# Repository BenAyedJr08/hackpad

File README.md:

# JR4 Macropad
to get an introduction to robotics, i decided to make a simple design of a pcb with 4 switches where i added some basic shortcuts for daily use.
# BOM :
- 1 SEED XIAO RP2040
- 4 MX switches
- 2 SK6812 rgb diodes
# Schematics :

# PCB :

# CAD :

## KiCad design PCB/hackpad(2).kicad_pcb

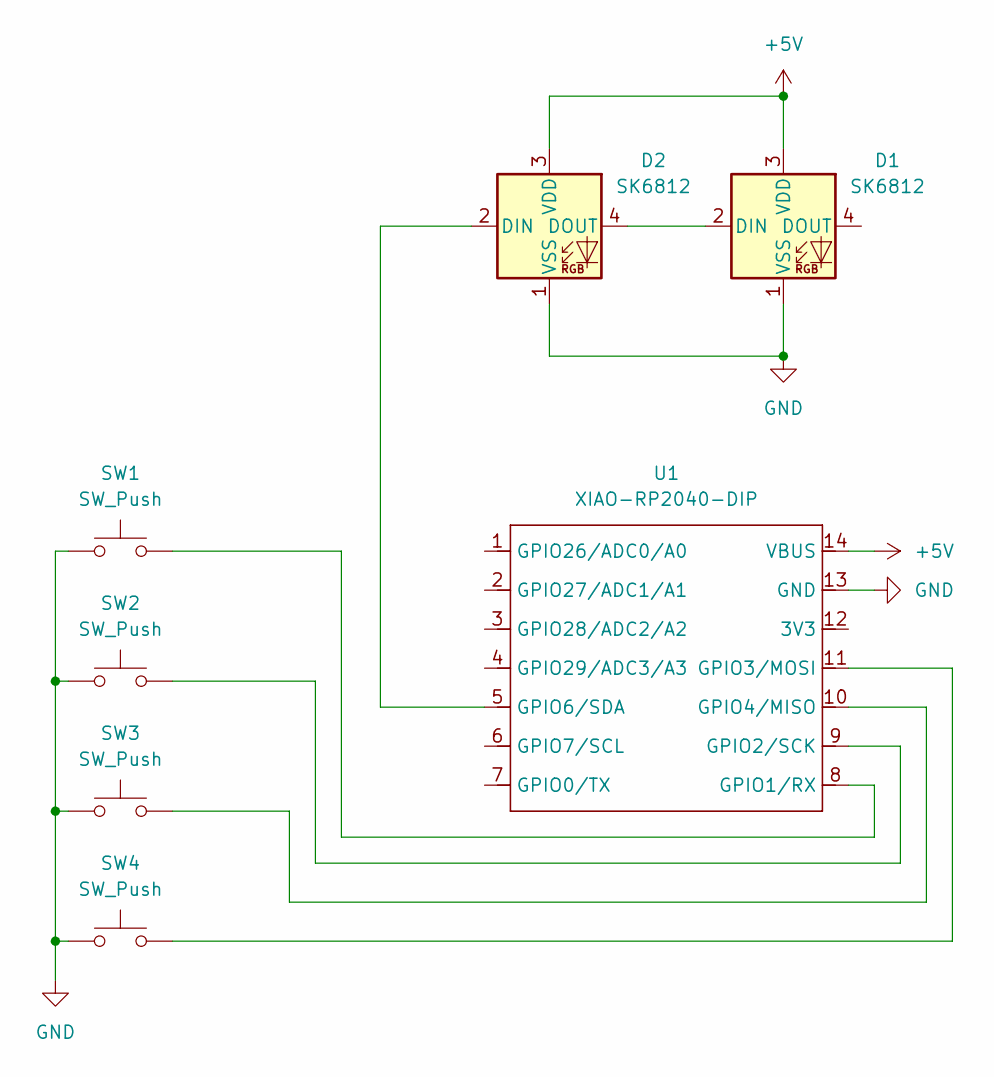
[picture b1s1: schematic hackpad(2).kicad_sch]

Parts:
D1, D2: SK6812; SK6812MINI-E_fixed
SW1, SW2, SW3, SW4: SW_Push; SW_Cherry_MX_1.00u_PCB
U1: XIAO-RP2040-DIP

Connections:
+5V: D1.3 (VDD), D2.3 (VDD), U1.14 (VBUS)
GND: D1.1 (VSS), D2.1 (VSS), SW1.1, SW2.1, SW3.1, SW4.1, U1.13 (GND)
unnamed: D1.2 (DIN), D2.4 (DOUT)
unnamed: D2.2 (DIN), U1.5 (GPIO6/SDA)
unnamed: SW1.2, U1.8 (GPIO1/RX)
unnamed: SW2.2, U1.9 (GPIO2/SCK)
unnamed: SW4.2, U1.11 (GPIO3/MOSI)
unnamed: SW3.2, U1.10 (GPIO4/MISO)

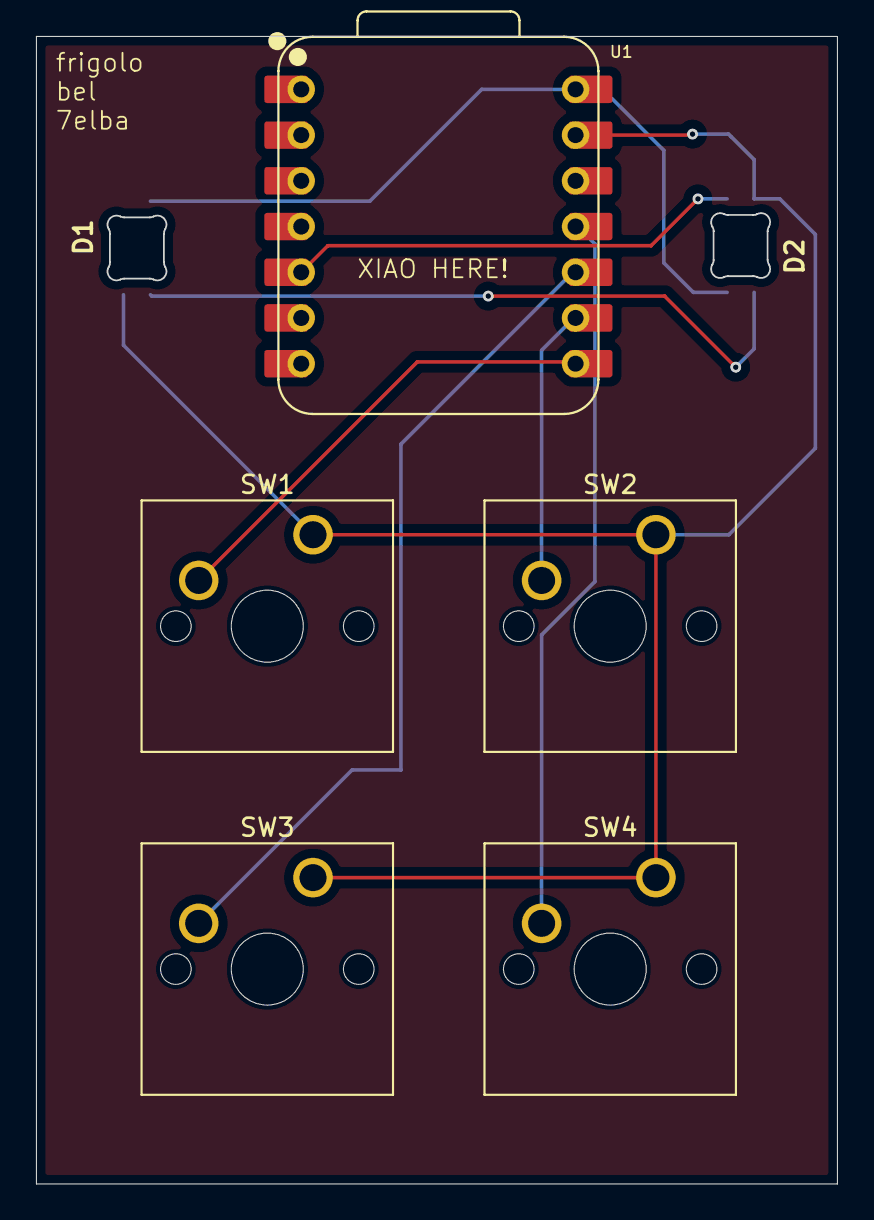
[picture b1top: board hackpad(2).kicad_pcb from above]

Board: 2 copper layers, 44.5 x 63.8 mm, 7 parts (0 on the bottom side), 8 nets.

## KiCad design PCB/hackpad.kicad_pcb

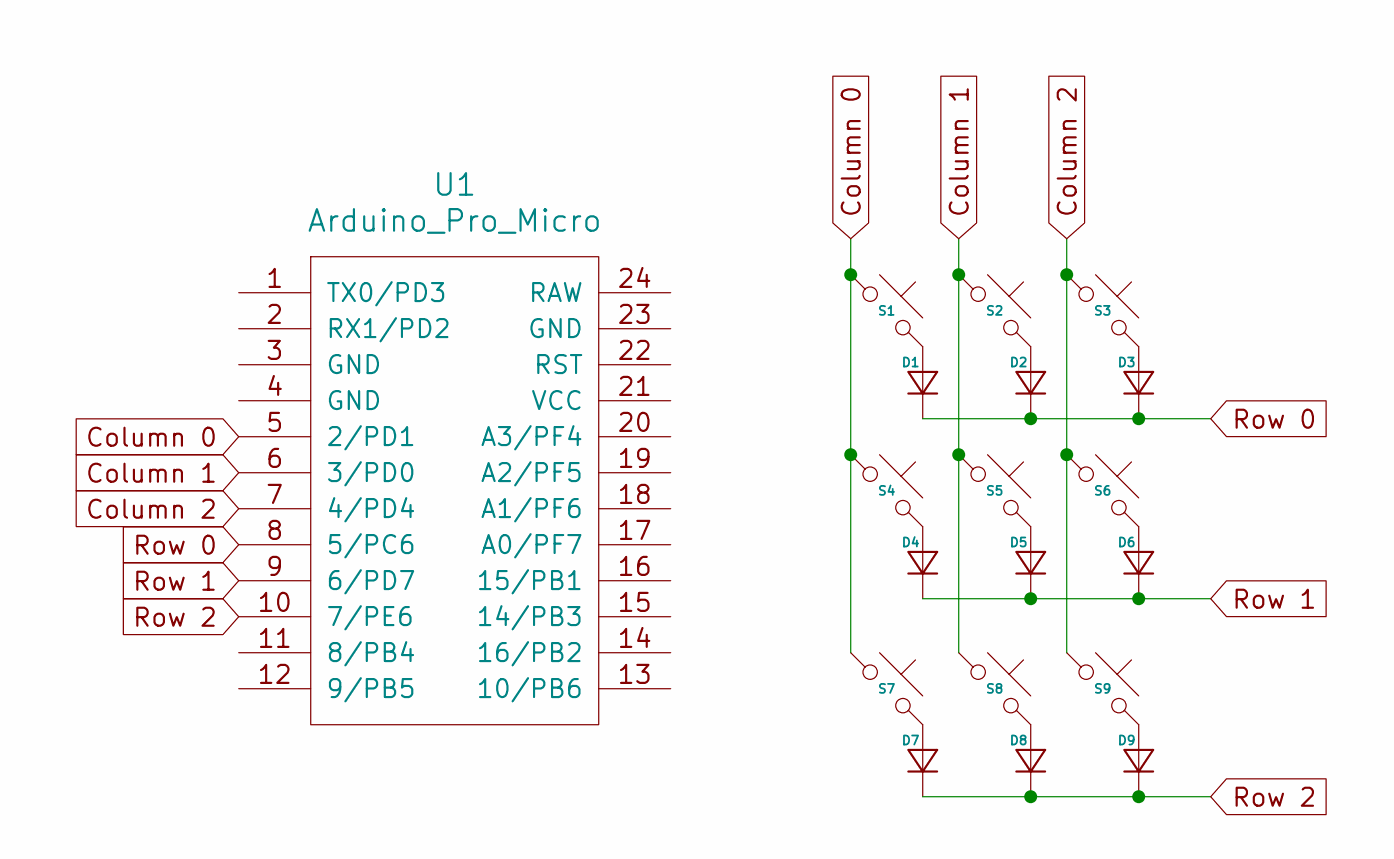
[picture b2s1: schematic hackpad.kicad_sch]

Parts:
D1, D2, D3, D4, D5, D6, D7, D8, D9: Diode_DO-35
S1, S2, S3, S4, S5, S6, S7, S8, S9: MX_PCB_1.00u
U1: Arduino_Pro_Micro

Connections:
Column 0: S1.1, S4.1, S7.1, U1.5 (2/PD1)
Column 1: S2.1, S5.1, S8.1, U1.6 (3/PD0)
Column 2: S3.1, S6.1, S9.1, U1.7 (4/PD4)
unnamed: D1.2 (A), S1.2
unnamed: D2.2 (A), S2.2
unnamed: D3.2 (A), S3.2
unnamed: D4.2 (A), S4.2
unnamed: D5.2 (A), S5.2
unnamed: D6.2 (A), S6.2
unnamed: D7.2 (A), S7.2
unnamed: D8.2 (A), S8.2
unnamed: D9.2 (A), S9.2
Row 0: D1.1 (K), D2.1 (K), D3.1 (K), U1.8 (5/PC6)
Row 1: D4.1 (K), D5.1 (K), D6.1 (K), U1.9 (6/PD7)
Row 2: D7.1 (K), D8.1 (K), D9.1 (K), U1.10 (7/PE6)

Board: 2 copper layers, 19 parts (0 on the bottom side), 15 nets, no tracks yet.
